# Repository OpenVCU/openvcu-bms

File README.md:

# OpenVCU BMS Hardware (`openvcu-bms`)

This repository contains the KiCad 10 schematics, PCB layouts, custom footprint/symbol libraries, Bill of Materials (BOM), and 3D CAD models for the **OpenVCU High-Voltage Battery Management System (BMS) Master Controller**.

## Ecosystem & Related Repositories

* **[OpenVCU Core (`OpenVCU/openvcu`)](https://github.com/OpenVCU/openvcu):** Core Vehicle Control Unit (VCU) firmware and system code.
* **[OpenVCU BMS Hardware (`OpenVCU/openvcu-bms`)](https://github.com/OpenVCU/openvcu-bms):** BMS Master hardware source files, KiCad 10 project, BOMs, and CAD models (this repository).
* **[OpenVCU BMS Firmware (`OpenVCU/openvcu-bms-firmware`)](https://github.com/OpenVCU/openvcu-bms-firmware):** Embedded C firmware (`STM32G474CCTx`) for the BMS Master controller, supporting the `INA228` power monitor and unified `LTC681x` / `ADBMS1818` isoSPI cell monitors.

---

## Hardware Specifications & Key Features

Designed for high-voltage electric vehicle battery packs (400V–800V class) with an emphasis on component availability, automated SMD PCBA manufacturing, reinforced galvanic isolation, and reliable operation from **-30°C** to **70°C**:

* **Microcontroller (`MCU.kicad_sch`):** STMicroelectronics **STM32G474CCTx** (LQFP-48, 170 MHz Cortex-M4F, 256 KB Flash).
* **Dual isoSPI Daisy-Chain Master (`MCU.kicad_sch`):**
  * Dual **LTC6820** (`U2, U11`) reversible isoSPI transceivers coupled through Pulse **HM2108NL** (`TR2, TR4`) isolation transformers to `J19` (`ISOSPI1`) and `J20` (`ISOSPI2`).
  * Supports redundant reversible ring topologies with **LTC6810**, **LTC6804**, **LTC6811**, **LTC6812**, **LTC6813**, and **ADBMS1818** slave modules.
* **High-Voltage Power & Current Monitoring (`PowerMonitor.kicad_sch`):**
  * **TI INA228AIDGSR** (`U16`) 20-bit I2C current/bus monitor with 40-bit hardware Coulomb accumulation across a **100 µΩ** Vishay `CSM2F-8518-L100J01` (`R29`) precision shunt.
  * Triple **TI AMC1301** (`U1, U12, U13`) reinforced isolated amplifiers paired with **OPA2197IDR** (`U15`) operational amplifiers for isolated pack and contactor voltage sensing.
* **Contactor, Precharge & Safety Interfaces (`Interfaces.kicad_sch`):**
  * 5x Nexperia **BUK9Y40-55B,115** (`LFPAK56`) automotive MOSFETs (`Q7, Q8, Q13, Q14, Q15`) driving Positive/Negative HV Contactors (`J1, J4`), Discharge/Charge loops (`J8, J9, J10`), and Cooling (`J2`).
  * Integrated high-voltage precharge circuit using a Standex-Meder **SHV12-1A85-78L3K** (`K1`) reed relay and 4x **135 Ω** wirewound power resistors (`R34, R44, R52, R53`).
  * Opto-isolated Charger/E-Stop sensing via **SFH617A-2X009T** (`U5, U9`) and **DMN6075S-7** small-signal MOSFETs.
* **Isolated CAN Bus (`CAN.kicad_sch`):**
  * **TI ISO1042DWVR** (`U8`) isolated CAN/CAN-FD transceiver powered via an **SN6501DBV** (`U4`) push-pull transformer driver (`TR1`) and **SZNUP2105L** (`D4`) bus ESD protection.
* **USB-C & Auto-Bootloader Interface (`USB.kicad_sch`):**
  * 16-pin **USB Type-C** receptacle (`J12`) with **SRV05-4** (`U17`) ESD protection and **CP2102C / CP2102N** (`U7`) USB-to-UART bridge, including hardware `DTR`/`RTS` auto-reset (`NRST`/`BOOT0`) circuitry.
* **Power Supply Architecture (`PowerSupply.kicad_sch`):**
  * Primary step-down stage built around the **TI LM5165YDRC** (`U19`) wide-input synchronous buck converter, plus isolated 5V rails (`SN6501DBV` + `WURTH-760390014` transformers).

---

## Repository & KiCad Project Structure

Requires **KiCad 10.0+** to open and edit the schematic and board files:

| File / Directory | Description |
| :--- | :--- |
| `BMS-Master.kicad_pro` | Main KiCad 10 project file |
| `BMS-Master.kicad_sch` | Top-level hierarchical root schematic |
| `Interfaces.kicad_sch` | High-current contactor drivers, HV precharge relay, and isolated inputs |
| `PowerMonitor.kicad_sch` | Shunt sensing (`INA228`), HV divider networks, and `AMC1301` isolated amplifiers |
| `PowerSupply.kicad_sch` | 12V input protection, `LM5165` buck converter, and power rails |
| `MCU.kicad_sch` | `STM32G474CCTx` MCU, dual `LTC6820` isoSPI masters, crystal, and headers |
| `CAN.kicad_sch` | Isolated CAN bus (`ISO1042DWVR`) and isolated `SN6501` power supply |
| `USB.kicad_sch` | USB-C receptacle, ESD array, and `CP2102` UART/bootloader bridge |
| `OpenVCU.kicad_sym` | Custom project schematic symbol library |
| `OpenVCU.pretty/` | Custom project PCB footprint library (`.kicad_mod`) |
| `CAD/` | 3D STEP (`.stp`) mechanical models for PCB assembly verification |
| `BMS-Master.csv` | Master Bill of Materials (BOM) |

---

## Credits & Lineage

Originally derived from the open-source DieBieMS / ENNOID-BMS hardware architecture and redesigned for the **OpenVCU** platform.

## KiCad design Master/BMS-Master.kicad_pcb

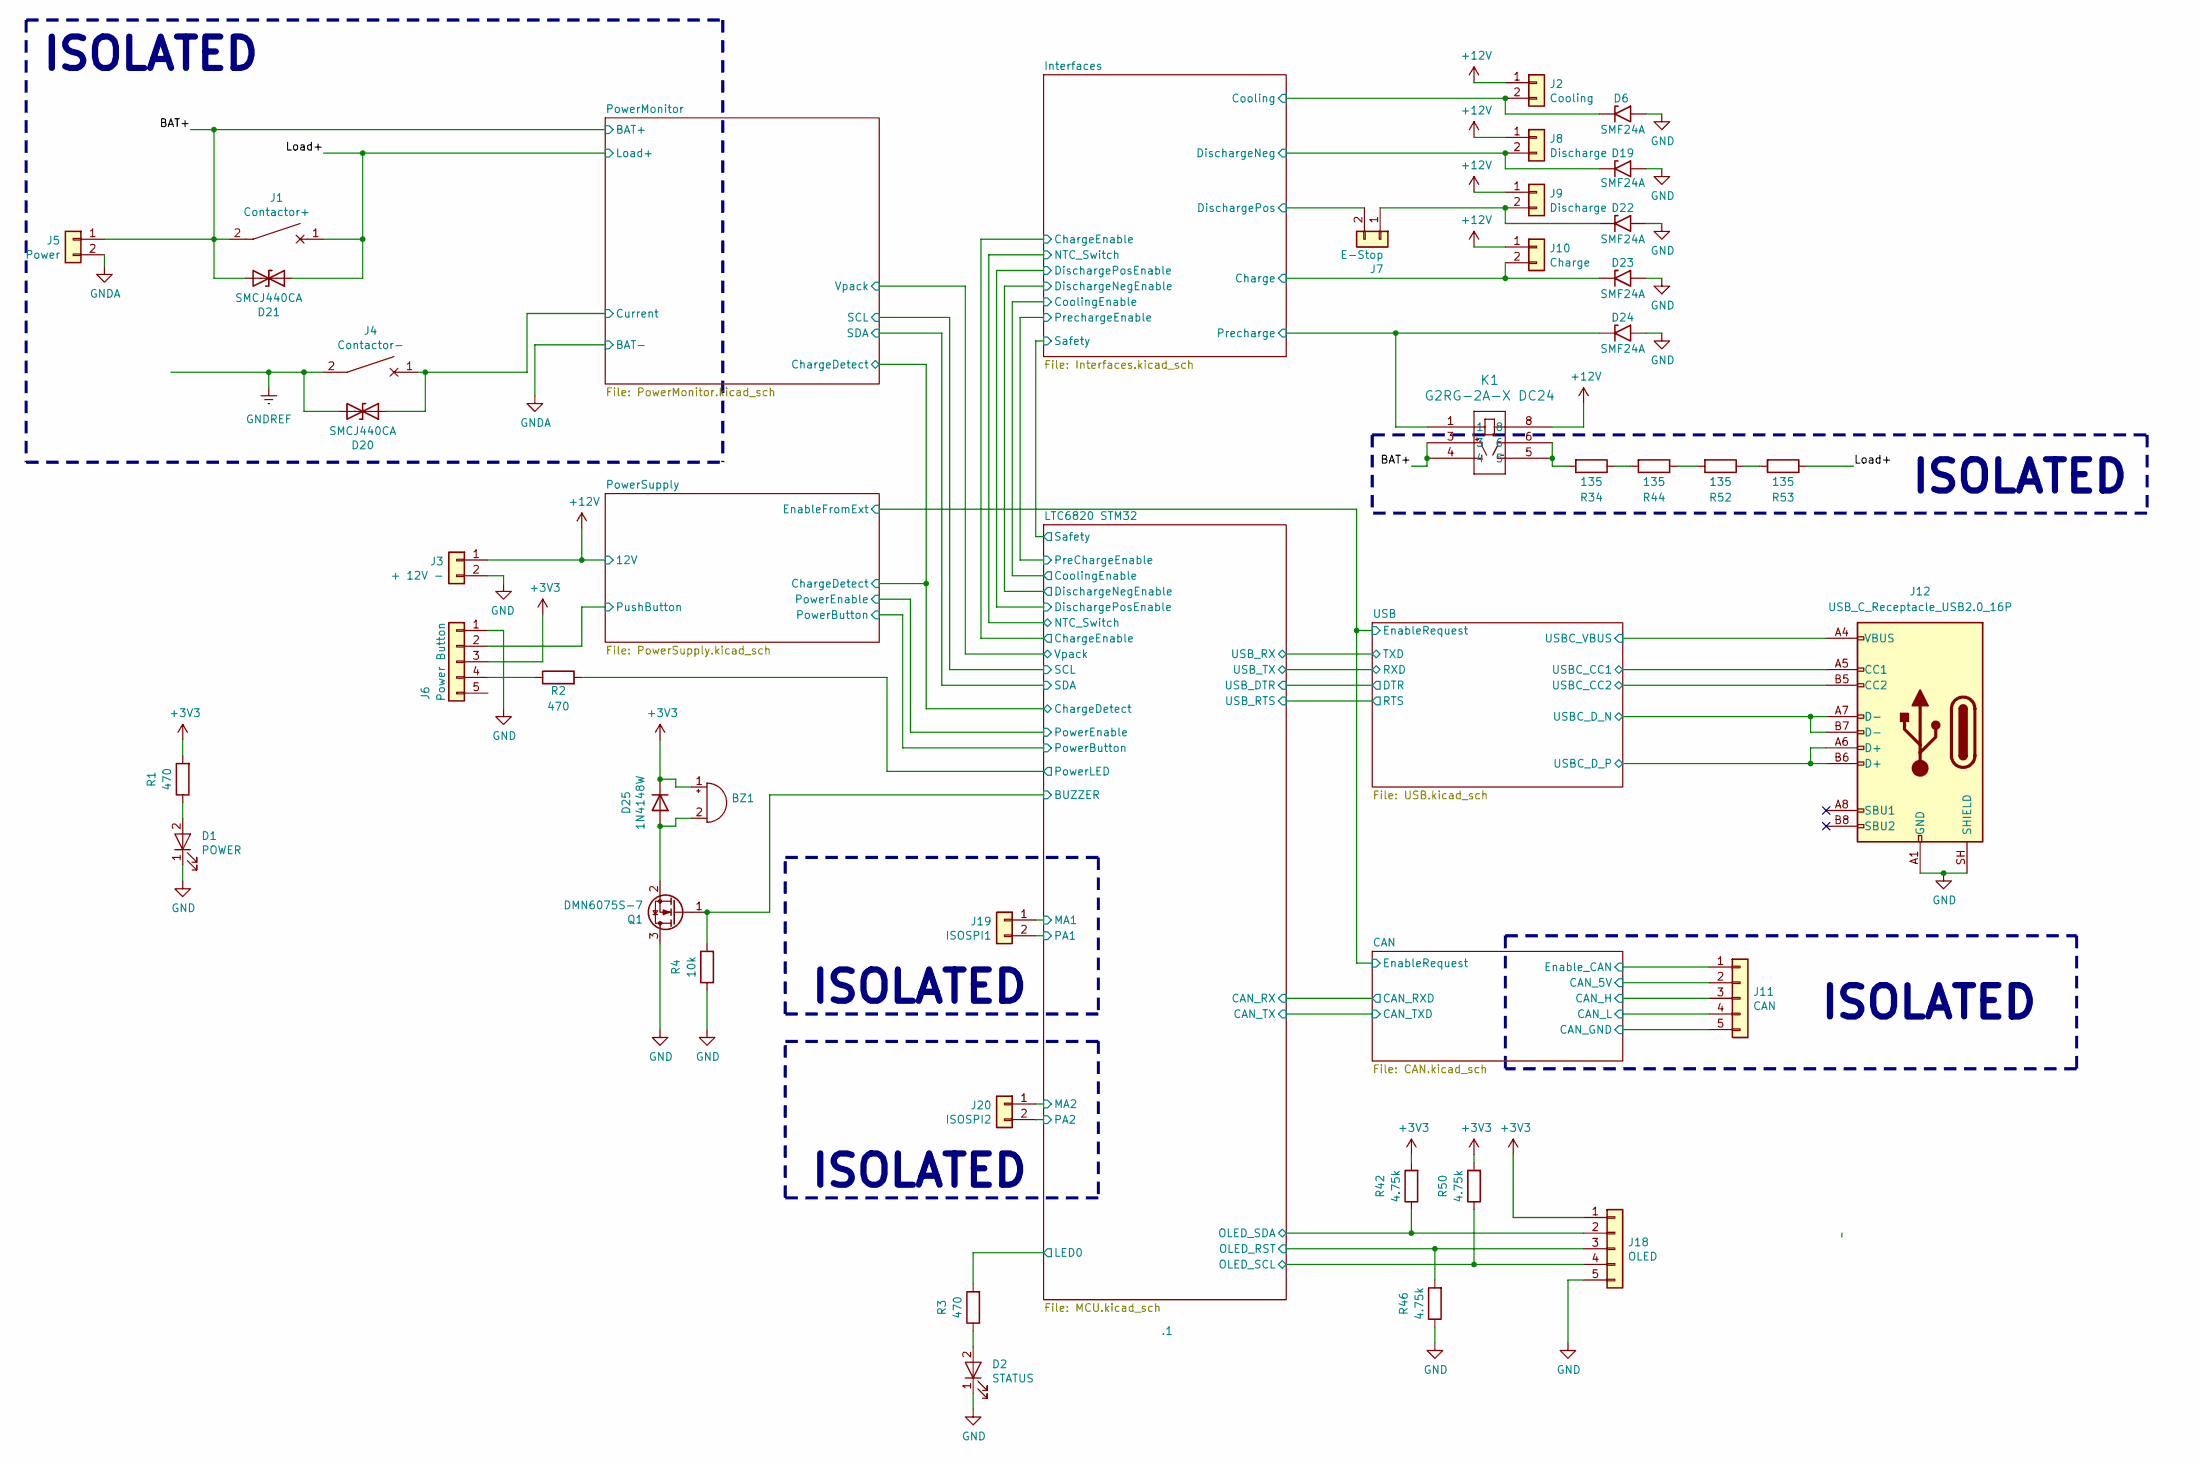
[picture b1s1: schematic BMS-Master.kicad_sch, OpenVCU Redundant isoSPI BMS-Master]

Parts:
.1: OpenVCU-Logo
BZ1: AI-1027-TWT-5V; BUZZER; MPN AI-1027-TWT-5V-2-R
D1: POWER; LED_0603_1608Metric; MPN SML-D12P8WT86C
D2: STATUS; LED_0603_1608Metric; MPN SML-D12P8WT86C
D6, D19, D22, D23, D24: SMF24A; D_SMF; MPN SMF24A
D20, D21: SMCJ440CA; D_SMC; MPN SMCJ440CA
D25: 1N4148W; D_SOD-123; MPN 1N4148W-7-F
J1: Contactor+; EVC500; MPN N/A
J2: Cooling; Pin_1x02-XL; MPN 70543-0001
J3: + 12V -; Pin_1x02-XL; MPN 70543-0001
J4: Contactor-; EVC500; MPN N/A
J5: Power; PhoenixContact_GMSTBVA_2,5_2-G_1x02_P7.50mm_Vertical; MPN 1766770
J6: Power Button; Molex_KK-254_AE-6410-05A_1x05_P2.54mm_Vertical; MPN 70543-0004
J7: E-Stop; Pin_1x02-XL; MPN 70543-0001
J8, J9: Discharge; Pin_1x02-XL; MPN 70543-0001
J10: Charge; Pin_1x02-XL; MPN 70543-0001
J11: CAN; Molex_KK-254_AE-6410-05A_1x05_P2.54mm_Vertical; MPN 70543-0004
J12: USB_C_Receptacle_USB2.0_16P; USB_C_Receptacle_HRO_TYPE-C-31-M-12; MPN TYPE-C-31-M-12
J18: OLED; Molex_KK-254_AE-6410-05A_1x05_P2.54mm_Vertical; MPN 70543-0004
J19: ISOSPI1; Pin_1x02-XL; MPN 70543-0001
J20: ISOSPI2; Pin_1x02-XL; MPN 70543-0001
K1: G2RG-2A-X DC24; G2RG-2A-X_OMR
Q1: DMN6075S-7; SOT-23; MPN DMN6075S-7
R1, R2, R3: 470; R_0603_1608Metric; MPN RC0603FR-07470RL
R4: 10k; R_0603_1608Metric; MPN RC0603FR-0710KL
R34, R44, R52, R53: 135; SM_3; MPN SMW3135RJT
R42, R46, R50: 4.75k; R_0603_1608Metric; MPN RC0603FR-074K75L

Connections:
+3V3: BZ1.1 (-), D25.1 (K), J6.3, J18.1, R1.2, R42.2, R50.2; also elsewhere on the board
+12V: J2.1, J3.1, J8.1, J9.1, J10.1, K1.8; also elsewhere on the board
/BAT+: D21.2 (A2), J1.2, J5.1, K1.3, K1.4; also elsewhere on the board
/CAN/CAN_5V: J11.2; also elsewhere on the board
/CAN/CAN_GND: J11.5; also elsewhere on the board
/CAN/CAN_H: J11.3; also elsewhere on the board
/CAN/CAN_L: J11.4; also elsewhere on the board
/CAN/Enable_CAN: J11.1; also elsewhere on the board
/Interfaces/Charge: D23.1 (A1), J10.2; also elsewhere on the board
/Interfaces/Cooling: D6.1 (A1), J2.2; also elsewhere on the board
/Interfaces/DischargeNeg: D19.1 (A1), J8.2; also elsewhere on the board
/Interfaces/DischargePos: J7.2; also elsewhere on the board
/Interfaces/Precharge: D24.1 (A1), K1.1; also elsewhere on the board
/LTC6820 STM32/BUZZER: Q1.1 (G), R4.2; also elsewhere on the board
/LTC6820 STM32/LED0: R3.2; also elsewhere on the board
/LTC6820 STM32/MA1: J19.1; also elsewhere on the board
/LTC6820 STM32/MA2: J20.1; also elsewhere on the board
/LTC6820 STM32/OLED_RST: J18.3, R46.2; also elsewhere on the board
/LTC6820 STM32/OLED_SCL: J18.4, R50.1; also elsewhere on the board
/LTC6820 STM32/OLED_SDA: J18.2, R42.1; also elsewhere on the board
/LTC6820 STM32/PA1: J19.2; also elsewhere on the board
/LTC6820 STM32/PA2: J20.2; also elsewhere on the board
/LTC6820 STM32/PowerLED: R2.2; also elsewhere on the board
/Load+: D21.1 (A1), J1.1, R53.1; also elsewhere on the board
/PowerMonitor/Current: D20.1 (A1), J4.1; also elsewhere on the board
/PowerSupply/PushButton: J6.2; also elsewhere on the board
/USB/D+: J12.A6 (D+), J12.B6 (D+); also elsewhere on the board
/USB/D-: J12.A7 (D-), J12.B7 (D-); also elsewhere on the board
/USB/USBC_CC1: J12.A5 (CC1); also elsewhere on the board
/USB/USBC_CC2: J12.B5 (CC2); also elsewhere on the board
/USB/USBC_VBUS: J12.A4 (VBUS), J12.A9 (VBUS), J12.B4 (VBUS), J12.B9 (VBUS); also elsewhere on the board
GND: D1.1 (K), D2.1 (K), D6.2 (A2), D19.2 (A2), D22.2 (A2), D23.2 (A2), D24.2 (A2), J3.2, J6.1, J12.A1 (GND), J12.A12 (GND), J12.B1 (GND), J12.B12 (GND), J12.SH (SHIELD), J18.5, Q1.3 (D), R4.1, R46.1; also elsewhere on the board
GNDA: J5.2; also elsewhere on the board
GNDREF: D20.2 (A2), J4.2; also elsewhere on the board
unnamed: BZ1.2 (+), D25.2 (A), Q1.2 (S)
unnamed: D1.2 (A), R1.1
unnamed: D2.2 (A), R3.1
unnamed: D22.1 (A1), J7.1, J9.2
unnamed: J6.4, R2.1
unnamed: K1.5, K1.6, R34.2
unnamed: R34.1, R44.2
unnamed: R44.1, R52.2
unnamed: R52.1, R53.2

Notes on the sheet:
ISOLATED

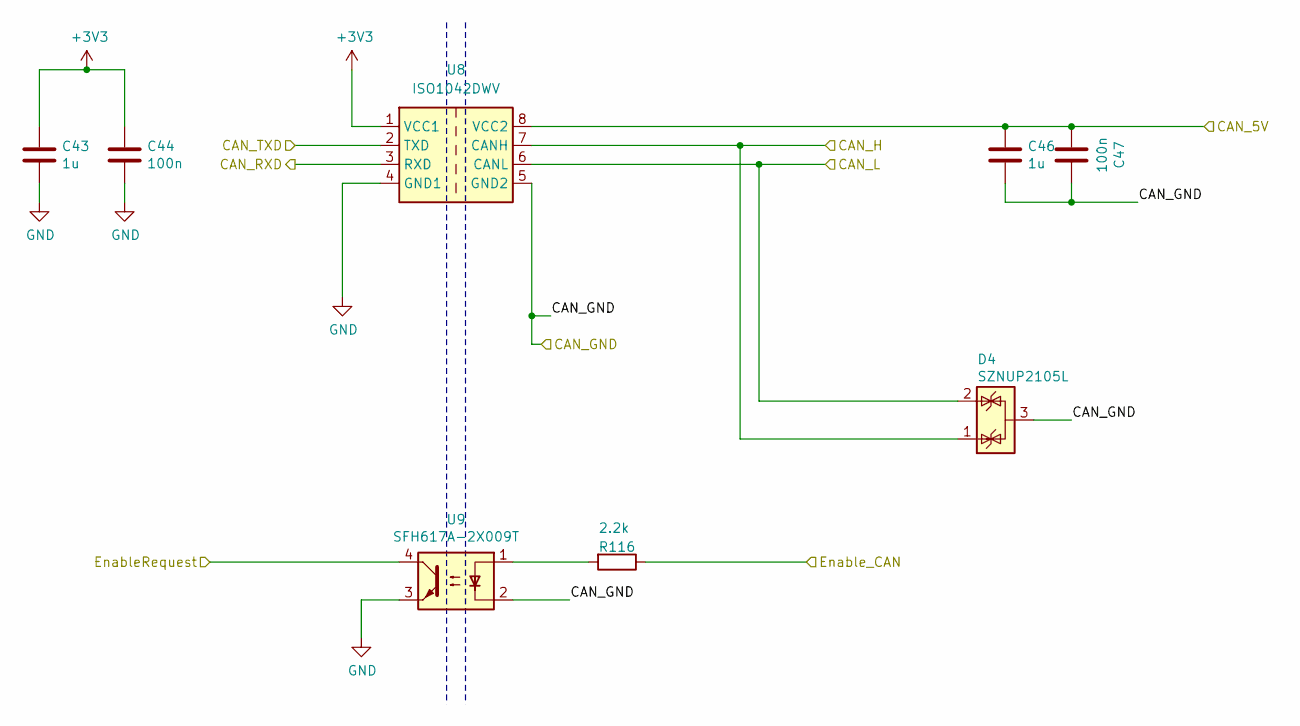
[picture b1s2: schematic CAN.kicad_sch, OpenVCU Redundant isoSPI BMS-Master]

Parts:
C43, C46: 1u; C_0603_1608Metric; MPN GRM188R71E105KA12D
C44, C47: 100n; C_0603_1608Metric; MPN GRM188R71E104KA01D
D4: SZNUP2105L; SOT-23; MPN SZNUP2105LT1G
R116: 2.2k; R_0603_1608Metric; MPN RC0603JR-072K2L
U8: ISO1042DWV; SOIC-8W_7.5x5.85mm_Pitch1.27mm; MPN ISO1042QDWVRQ1
U9: SFH617A-2X009T; SMDIP-4_W9.53mm_Clearance8mm; MPN SFH617A-2X009T

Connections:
+3V3: C43.1, C44.1, U8.1 (VCC1); also elsewhere on the board
/CAN/CAN_5V: C46.1, C47.2, U8.8 (VCC2); also elsewhere on the board
/CAN/CAN_GND: C46.2, C47.1, D4.3 (A), U8.5 (GND2), U9.2; also elsewhere on the board
/CAN/CAN_H: D4.1 (K), U8.7 (CANH); also elsewhere on the board
/CAN/CAN_L: D4.2 (K), U8.6 (CANL); also elsewhere on the board
/CAN/CAN_RXD: U8.3 (RXD); also elsewhere on the board
/CAN/CAN_TXD: U8.2 (TXD); also elsewhere on the board
/CAN/EnableRequest: U9.4; also elsewhere on the board
/CAN/Enable_CAN: R116.1; also elsewhere on the board
GND: C43.2, C44.2, U8.4 (GND1), U9.3; also elsewhere on the board
unnamed: R116.2, U9.1

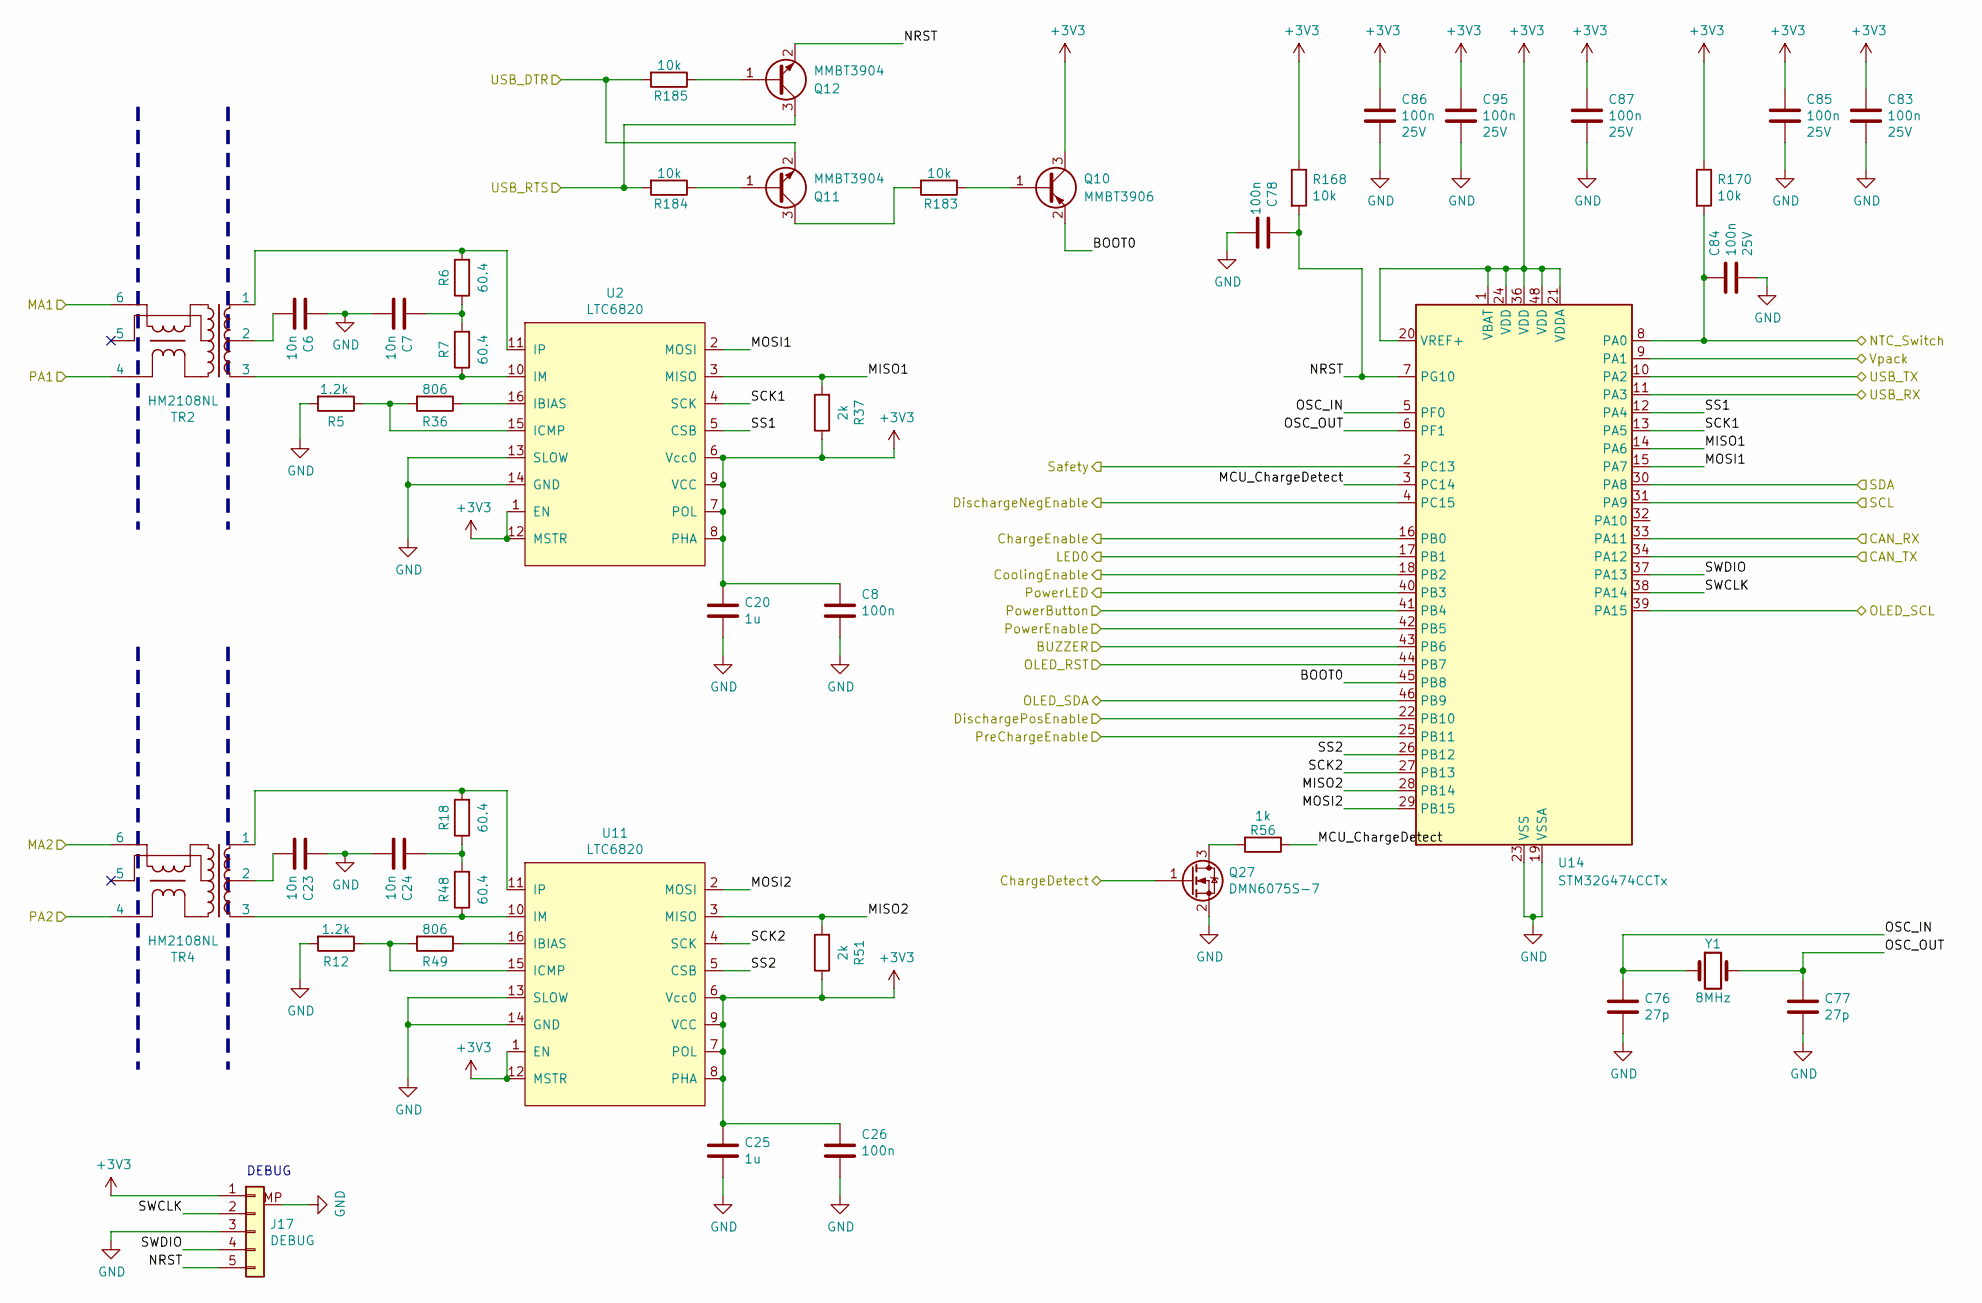
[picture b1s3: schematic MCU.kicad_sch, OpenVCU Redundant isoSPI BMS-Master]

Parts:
C6, C7, C23, C24: 10n; C_0603_1608Metric; MPN GRM188R71H103KA01D
C8, C26, C83, C84, C85, C86, C87, C95: 100n; C_0603_1608Metric; Voltage 25V; MPN GRM188R71E104KA01D
C20, C25: 1u; C_0603_1608Metric; MPN GRM188R71E105KA12D
C76, C77: 27p; C_0603_1608Metric; Voltage 50V; MPN GRM1885C1H270JA01D
C78: 100n; C_0603_1608Metric; MPN GRM188R71E104KA01D
J17: DEBUG; Molex_PicoBlade_53398-0571_1x05-1MP_P1.25mm_Vertical; MPN 53398-0571
Q10: MMBT3906; SOT-23; MPN MMBT3906LT1G
Q11, Q12: MMBT3904; SOT-23; MPN MMBT3904LT1G
Q27: DMN6075S-7; SOT-23; MPN DMN6075S-7
R5, R12: 1.2k; R_0603_1608Metric; MPN RC0603FR-071K2L
R6, R7, R18, R48: 60.4; R_0603_1608Metric; MPN RC0603FR-0760R4L
R36, R49: 806; R_0603_1608Metric; MPN RC0603FR-07806RL
R37, R51: 2k; R_0603_1608Metric; MPN RC0603FR-072KL
R56: 1k; R_0603_1608Metric; MPN MCR03EZPFX1001
R168, R170, R183, R184, R185: 10k; R_0603_1608Metric; MPN RC0603FR-0710KL
TR2, TR4: HM2108NL; MPN HM2108NL
U2, U11: LTC6820; MSOP-16_3x4.039mm_P0.5mm; MPN LTC6820IMS#PBF
U14: STM32G474CCTx; LQFP-48_7x7mm_P0.5mm; MPN STM32G474CCT6
Y1: 8MHz; Crystal_SMD_Abracon_ABM3-2Pin_5.0x3.2mm; MPN ABM3-8.000MHZ-D2Y-T

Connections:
+3V3: C8.1, C20.2, C25.2, C26.1, C83.1, C85.1, C86.1, C87.1, C95.1, J17.1, Q10.3 (C), R37.1, R51.1, R168.1, R170.1, U2.1 (EN), U2.6 (Vcc0), U2.7 (POL), U2.8 (PHA), U2.9 (VCC), U2.12 (MSTR), U11.1 (EN), U11.6 (Vcc0), U11.7 (POL), U11.8 (PHA), U11.9 (VCC), U11.12 (MSTR), U14.1 (VBAT), U14.20 (VREF+), U14.21 (VDDA), U14.24 (VDD), U14.36 (VDD), U14.48 (VDD); also elsewhere on the board
/CAN/CAN_RXD: U14.33 (PA11); also elsewhere on the board
/CAN/CAN_TXD: U14.34 (PA12); also elsewhere on the board
/Interfaces/ChargeEnable: U14.16 (PB0); also elsewhere on the board
/Interfaces/CoolingEnable: U14.18 (PB2); also elsewhere on the board
/Interfaces/DischargeNegEnable: U14.4 (PC15); also elsewhere on the board
/Interfaces/DischargePosEnable: U14.22 (PB10); also elsewhere on the board
/Interfaces/NTC_Switch: C84.1, R170.2, U14.8 (PA0); also elsewhere on the board
/Interfaces/PrechargeEnable: U14.25 (PB11); also elsewhere on the board
/Interfaces/Safety: U14.2 (PC13); also elsewhere on the board
/LTC6820 STM32/BOOT0: Q10.2 (E), U14.45 (PB8)
/LTC6820 STM32/BUZZER: U14.43 (PB6); also elsewhere on the board
/LTC6820 STM32/LED0: U14.17 (PB1); also elsewhere on the board
/LTC6820 STM32/MA1: TR2.6; also elsewhere on the board
/LTC6820 STM32/MA2: TR4.6; also elsewhere on the board
/LTC6820 STM32/MCU_ChargeDetect: R56.1, U14.3 (PC14)
/LTC6820 STM32/MISO1: R37.2, U2.3 (MISO), U14.14 (PA6)
/LTC6820 STM32/MISO2: R51.2, U11.3 (MISO), U14.28 (PB14)
/LTC6820 STM32/MOSI1: U2.2 (MOSI), U14.15 (PA7)
/LTC6820 STM32/MOSI2: U11.2 (MOSI), U14.29 (PB15)
/LTC6820 STM32/NRST: C78.1, J17.5, Q12.2 (E), R168.2, U14.7 (PG10)
/LTC6820 STM32/OLED_RST: U14.44 (PB7); also elsewhere on the board
/LTC6820 STM32/OLED_SCL: U14.39 (PA15); also elsewhere on the board
/LTC6820 STM32/OLED_SDA: U14.46 (PB9); also elsewhere on the board
/LTC6820 STM32/OSC_IN: C76.1, U14.5 (PF0), Y1.1
/LTC6820 STM32/OSC_OUT: C77.1, U14.6 (PF1), Y1.2
/LTC6820 STM32/PA1: TR2.4; also elsewhere on the board
/LTC6820 STM32/PA2: TR4.4; also elsewhere on the board
/LTC6820 STM32/PowerButton: U14.41 (PB4); also elsewhere on the board
/LTC6820 STM32/PowerEnable: U14.42 (PB5); also elsewhere on the board
/LTC6820 STM32/PowerLED: U14.40 (PB3); also elsewhere on the board
/LTC6820 STM32/SCK1: U2.4 (SCK), U14.13 (PA5)
/LTC6820 STM32/SCK2: U11.4 (SCK), U14.27 (PB13)
/LTC6820 STM32/SCL: U14.31 (PA9); also elsewhere on the board
/LTC6820 STM32/SDA: U14.30 (PA8); also elsewhere on the board
/LTC6820 STM32/SS1: U2.5 (CSB), U14.12 (PA4)
/LTC6820 STM32/SS2: U11.5 (CSB), U14.26 (PB12)
/LTC6820 STM32/SWCLK: J17.2, U14.38 (PA14)
/LTC6820 STM32/SWDIO: J17.4, U14.37 (PA13)
/LTC6820 STM32/USB_DTR: Q11.2 (E), R185.2; also elsewhere on the board
/LTC6820 STM32/USB_RTS: Q12.3 (C), R184.2; also elsewhere on the board
/LTC6820 STM32/USB_RX: U14.11 (PA3); also elsewhere on the board
/LTC6820 STM32/USB_TX: U14.10 (PA2); also elsewhere on the board
/LTC6820 STM32/Vpack: U14.9 (PA1); also elsewhere on the board
/PowerSupply/ChargeDetect: Q27.1 (G); also elsewhere on the board
GND: C6.2, C7.1, C8.2, C20.1, C23.2, C24.1, C25.1, C26.2, C76.2, C77.2, C78.2, C83.2, C84.2, C85.2, C86.2, C87.2, C95.2, J17.3, J17.MP, Q27.2 (S), R5.2, R12.2, U2.13 (SLOW), U2.14 (GND), U11.13 (SLOW), U11.14 (GND), U14.19 (VSSA), U14.23 (VSS), U14.35 (VSS), U14.47 (VSS); also elsewhere on the board
unnamed: C6.1, TR2.2
unnamed: C7.2, R6.1, R7.2
unnamed: C23.1, TR4.2
unnamed: C24.2, R18.1, R48.2
unnamed: Q10.1 (B), R183.1
unnamed: Q11.1 (B), R184.1
unnamed: Q11.3 (C), R183.2
unnamed: Q12.1 (B), R185.1
unnamed: Q27.3 (D), R56.2
unnamed: R36.1, U2.16 (IBIAS)
unnamed: R5.1, R36.2, U2.15 (ICMP)
unnamed: R7.1, TR2.3, U2.10 (IM)
unnamed: R6.2, TR2.1, U2.11 (IP)
unnamed: R49.1, U11.16 (IBIAS)
unnamed: R12.1, R49.2, U11.15 (ICMP)
unnamed: R48.1, TR4.3, U11.10 (IM)
unnamed: R18.2, TR4.1, U11.11 (IP)

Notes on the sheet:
DEBUG

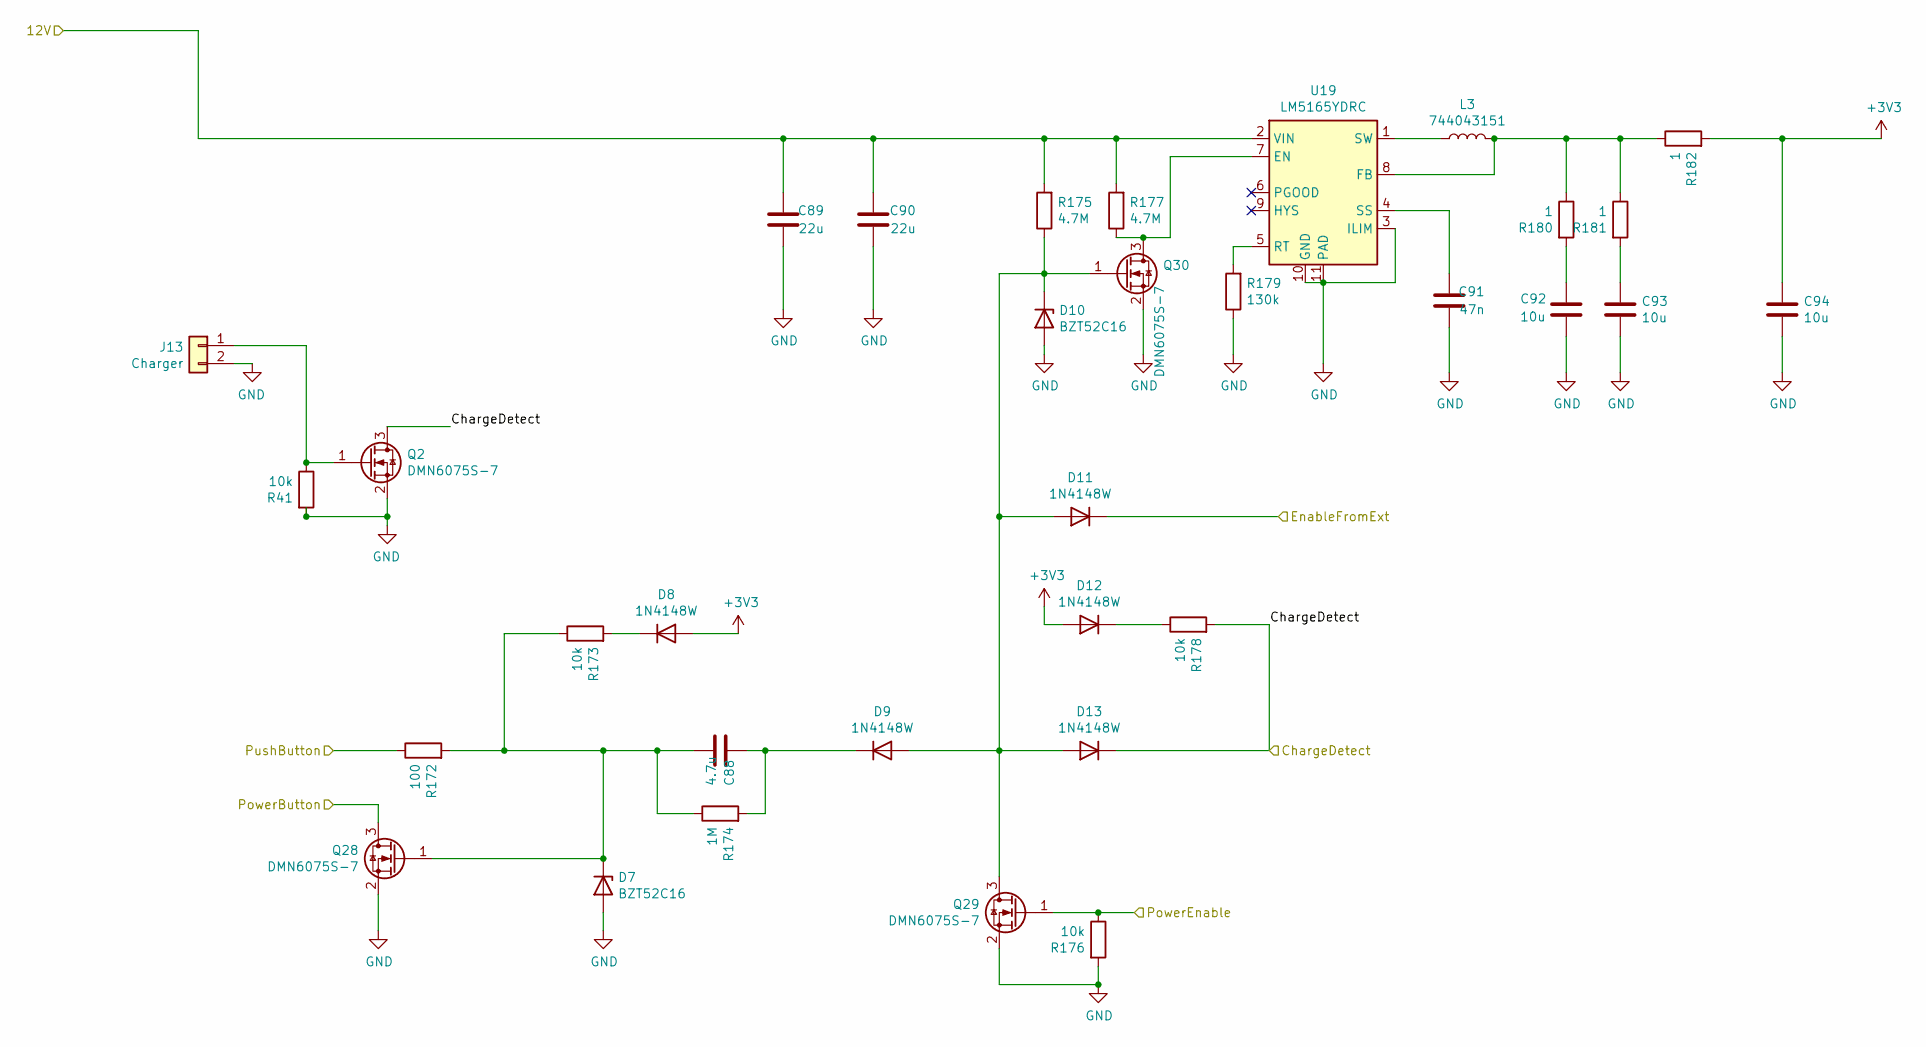
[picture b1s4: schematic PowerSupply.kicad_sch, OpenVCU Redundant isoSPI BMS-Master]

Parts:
C88: 4.7u; C_0805_2012Metric; MPN GRM21BR71E475KA73L
C89, C90: 22u; C_0805_2012Metric; MPN CL21A226MAQNNNE
C91: 47n; C_0603_1608Metric; Voltage 100V; MPN GCM188R71H473KA55D
C92, C93, C94: 10u; C_0805_2012Metric; MPN CL21A106KAYNNNE
D7, D10: BZT52C16; D_SOD-123; MPN BZT52C16-E3-08
D8, D9, D11, D12, D13: 1N4148W; D_SOD-123; MPN 1N4148W-7-F
J13: Charger; Pin_1x02-XL; MPN 70543-0001
L3: 744043151; L_Wuerth_WE-PD2-Typ-MS; MPN 744043151
Q2, Q28, Q29, Q30: DMN6075S-7; SOT-23; MPN DMN6075S-7
R41, R173, R176, R178: 10k; R_0603_1608Metric; MPN RC0603FR-0710KL
R172: 100; R_0603_1608Metric; MPN RC0603FR-07100RL
R174: 1M; R_0603_1608Metric; MPN RC0603JR-071ML
R175, R177: 4.7M; R_0603_1608Metric; MPN RC0603FR-074M7L
R179: 130k; R_0603_1608Metric; MPN RC0603FR-07130KL
R180, R181, R182: 1; R_0603_1608Metric; MPN RC0603FR-071RL
U19: LM5165YDRC; Texas_S-PVSON-N10_ThermalVias; MPN LM5165YDRCR

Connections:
+3V3: C94.1, D8.2 (A), D12.2 (A), R182.2; also elsewhere on the board
+12V: C89.2, C90.2, R175.2, R177.2, U19.2 (VIN); also elsewhere on the board
/CAN/EnableRequest: D11.1 (K); also elsewhere on the board
/LTC6820 STM32/PowerButton: Q28.3 (D); also elsewhere on the board
/LTC6820 STM32/PowerEnable: Q29.1 (G), R176.1; also elsewhere on the board
/PowerSupply/ChargeDetect: D13.1 (K), Q2.3 (D), R178.2; also elsewhere on the board
/PowerSupply/PushButton: R172.1; also elsewhere on the board
GND: C89.1, C90.1, C91.1, C92.2, C93.2, C94.2, D7.2 (A), D10.2 (A), J13.2, Q2.2 (S), Q28.2 (S), Q29.2 (S), Q30.2 (S), R41.2, R176.2, R179.1, U19.3 (ILIM), U19.10 (GND), U19.11 (PAD); also elsewhere on the board
unnamed: C92.1, R180.2
unnamed: C93.1, R181.2
unnamed: C88.1, D7.1 (K), Q28.1 (G), R172.2, R173.1, R174.1
unnamed: D8.1 (K), R173.2
unnamed: C88.2, D9.1 (K), R174.2
unnamed: D9.2 (A), D10.1 (K), D11.2 (A), D13.2 (A), Q29.3 (D), Q30.1 (G), R175.1
unnamed: D12.1 (K), R178.1
unnamed: J13.1, Q2.1 (G), R41.1
unnamed: Q30.3 (D), R177.1, U19.7 (EN)
unnamed: L3.2, R180.1, R181.1, R182.1, U19.8 (FB)
unnamed: R179.2, U19.5 (RT)
unnamed: C91.2, U19.4 (SS)
unnamed: L3.1, U19.1 (SW)

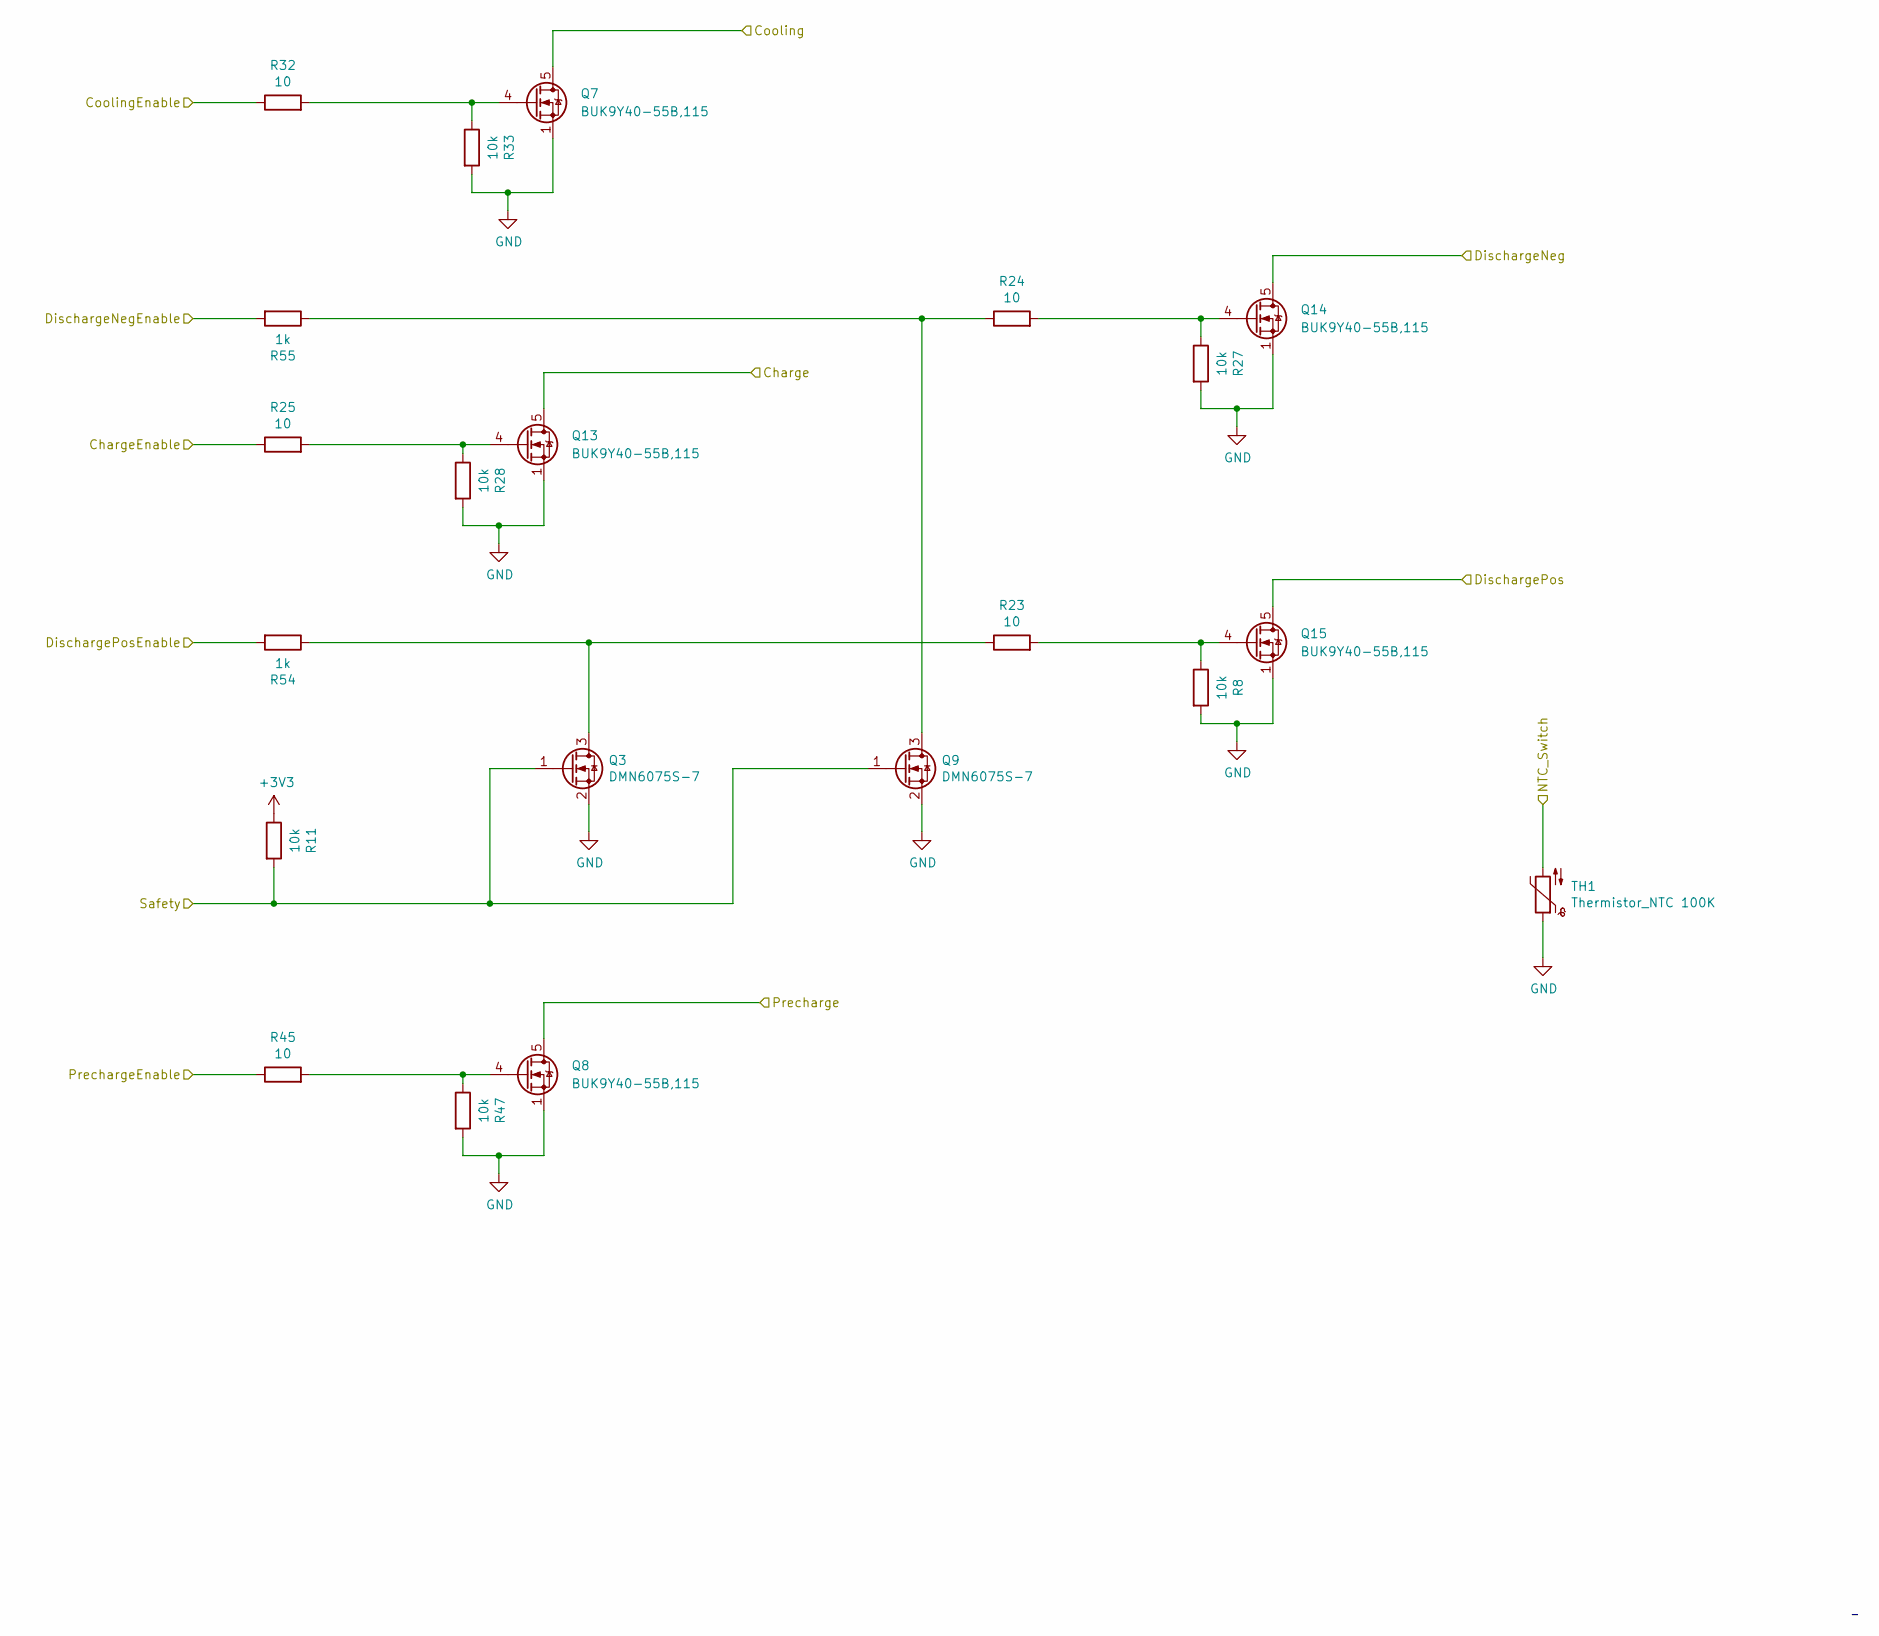
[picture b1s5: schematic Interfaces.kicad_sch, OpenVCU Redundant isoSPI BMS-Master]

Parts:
Q3, Q9: DMN6075S-7; SOT-23; MPN DMN6075S-7
Q7, Q8, Q13, Q14, Q15: BUK9Y40-55B,115; LFPAK56; MPN BUK9Y40-55B,115
R8, R11, R27, R28, R33, R47: 10k; R_0603_1608Metric; MPN RC0603FR-0710KL
R23, R24, R25, R32, R45: 10; R_0603_1608Metric; MPN RC0603JR-0710RL
R54, R55: 1k; R_0603_1608Metric; MPN MCR03EZPFX1001
TH1: Thermistor_NTC 100K; R_0805_2012Metric; MPN SDNT2012X104F4250FTF

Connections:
+3V3: R11.1; also elsewhere on the board
/Interfaces/Charge: Q13.5 (D); also elsewhere on the board
/Interfaces/ChargeEnable: R25.1; also elsewhere on the board
/Interfaces/Cooling: Q7.5 (D); also elsewhere on the board
/Interfaces/CoolingEnable: R32.1; also elsewhere on the board
/Interfaces/DischargeNeg: Q14.5 (D); also elsewhere on the board
/Interfaces/DischargeNegEnable: R55.2; also elsewhere on the board
/Interfaces/DischargePos: Q15.5 (D); also elsewhere on the board
/Interfaces/DischargePosEnable: R54.2; also elsewhere on the board
/Interfaces/NTC_Switch: TH1.2; also elsewhere on the board
/Interfaces/Precharge: Q8.5 (D); also elsewhere on the board
/Interfaces/PrechargeEnable: R45.1; also elsewhere on the board
/Interfaces/Safety: Q3.1 (G), Q9.1 (G), R11.2; also elsewhere on the board
GND: Q3.2 (S), Q7.1 (S), Q7.2 (S), Q7.3 (S), Q8.1 (S), Q8.2 (S), Q8.3 (S), Q9.2 (S), Q13.1 (S), Q13.2 (S), Q13.3 (S), Q14.1 (S), Q14.2 (S), Q14.3 (S), Q15.1 (S), Q15.2 (S), Q15.3 (S), R8.2, R27.2, R28.2, R33.2, R47.2, TH1.1; also elsewhere on the board
unnamed: Q3.3 (D), R23.1, R54.1
unnamed: Q7.4 (G), R32.2, R33.1
unnamed: Q8.4 (G), R45.2, R47.1
unnamed: Q9.3 (D), R24.1, R55.1
unnamed: Q13.4 (G), R25.2, R28.1
unnamed: Q14.4 (G), R24.2, R27.1
unnamed: Q15.4 (G), R8.1, R23.2
